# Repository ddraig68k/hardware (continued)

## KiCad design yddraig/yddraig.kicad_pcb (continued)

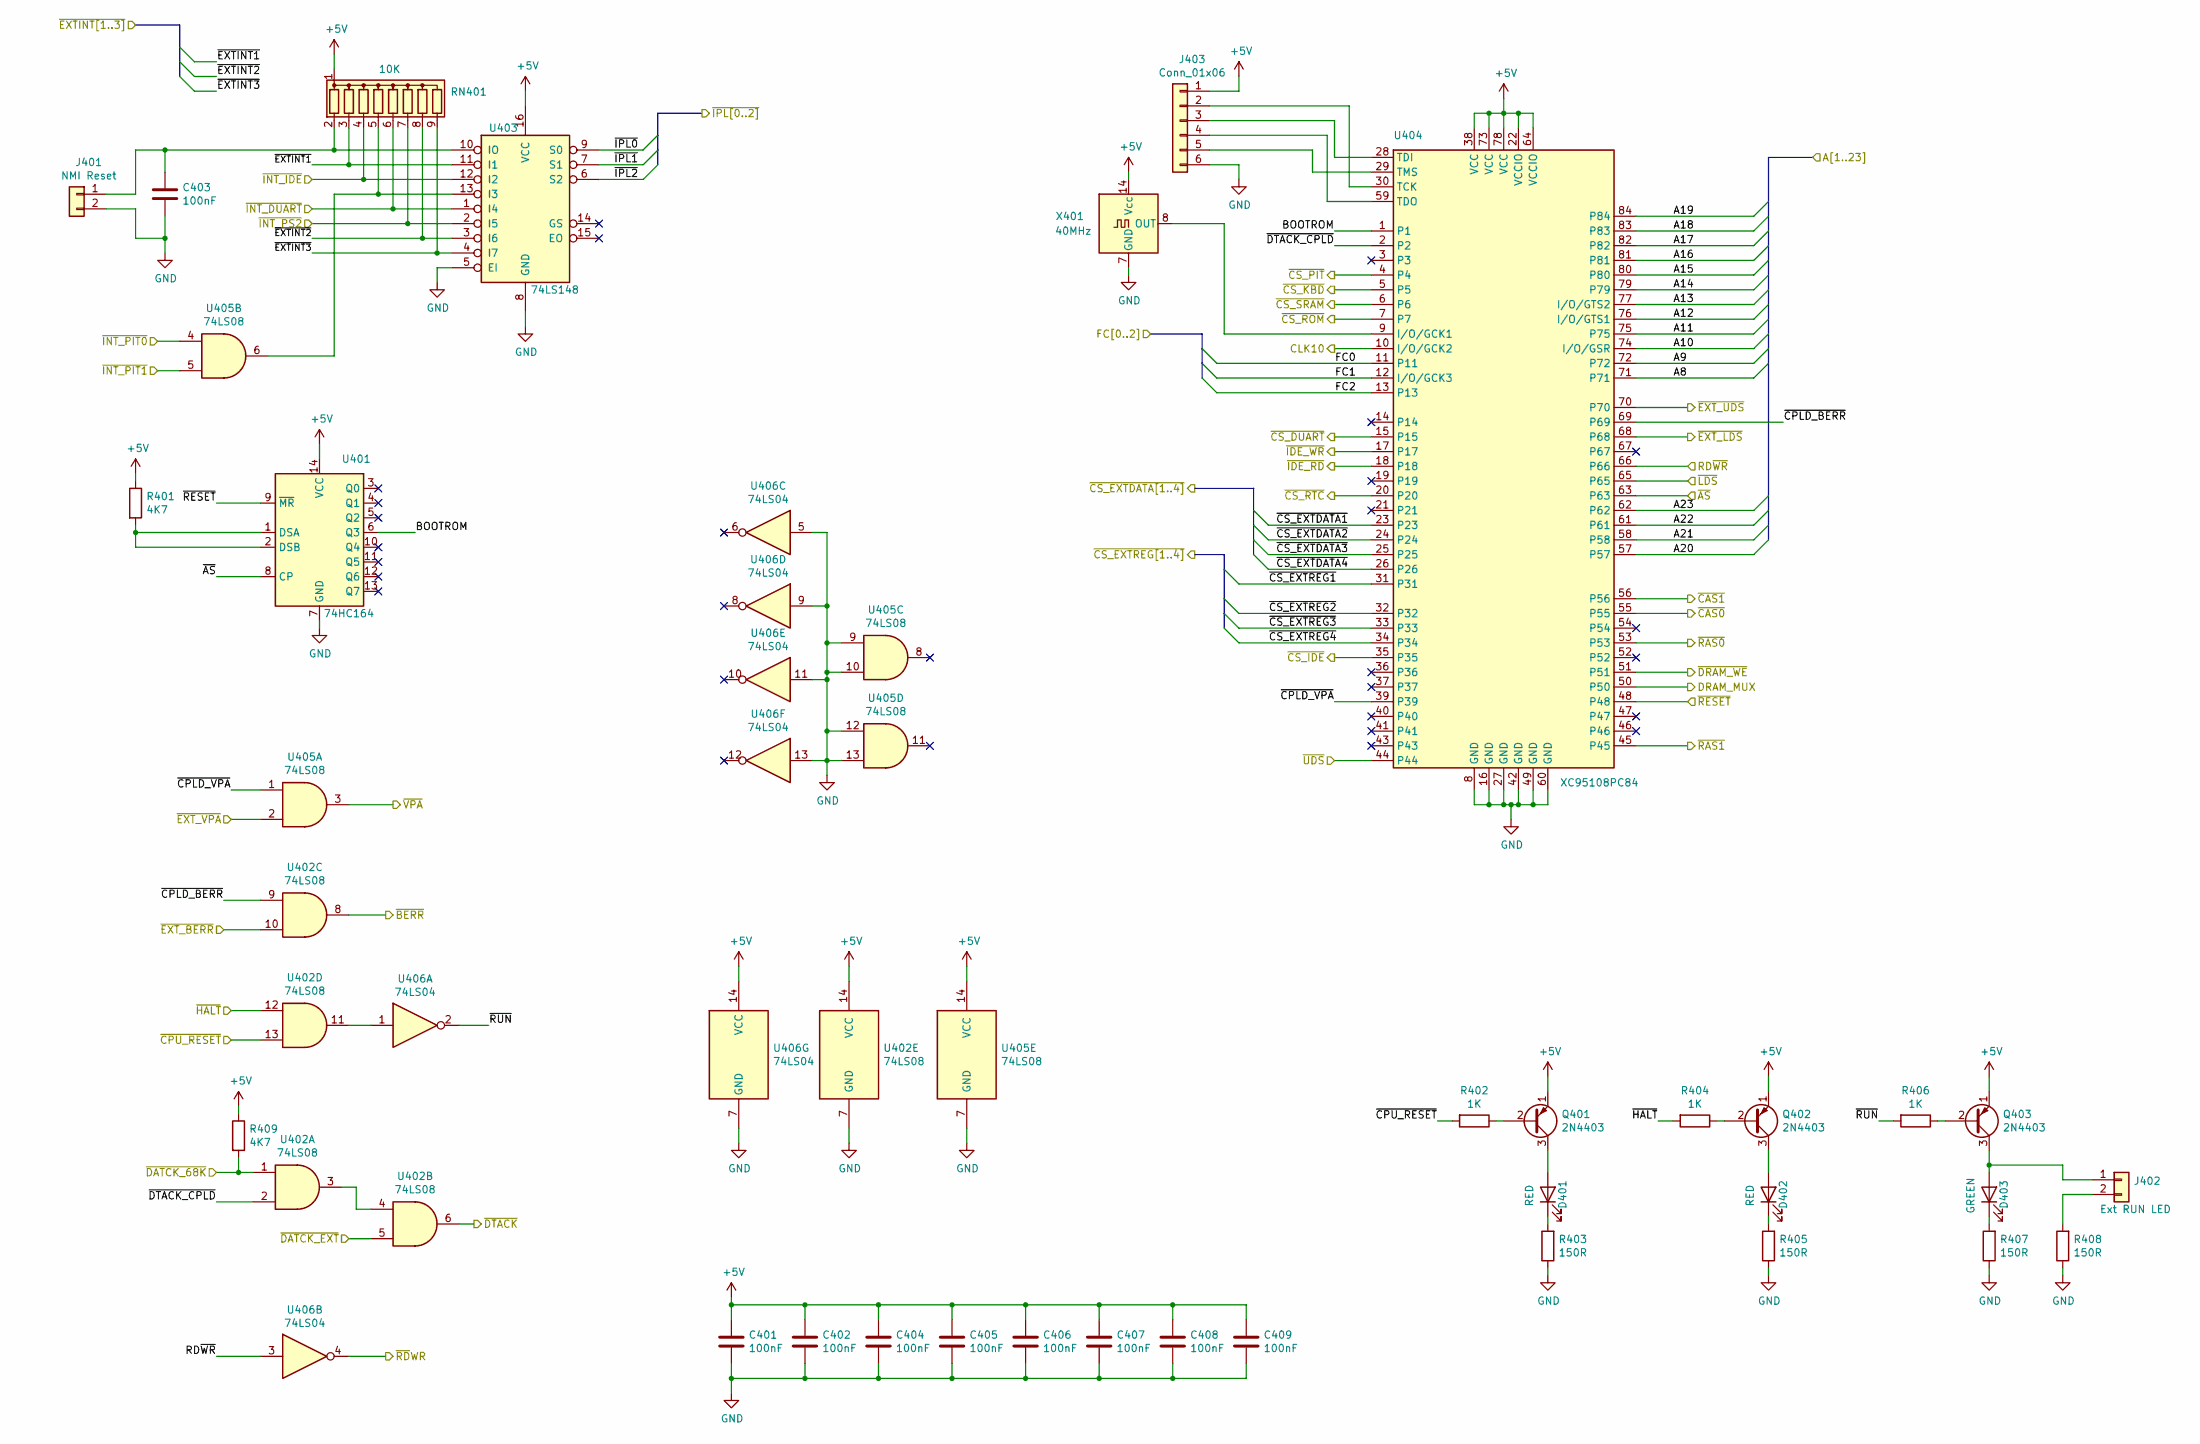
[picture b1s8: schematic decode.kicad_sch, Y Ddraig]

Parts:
C401, C402, C403, C404, C405, C406, C407, C408, C409: 100nF; C_Disc_D3.8mm_W2.6mm_P2.50mm
D401, D402: RED; LED_D5.0mm
D403: GREEN; LED_D5.0mm
J401: NMI Reset; PinHeader_1x02_P2.54mm_Vertical
J402: Ext RUN LED; PinHeader_1x02_P2.54mm_Vertical
J403: Conn_01x06; PinHeader_1x06_P2.54mm_Vertical
Q401, Q402, Q403: 2N4403; TO-92
R401, R409: 4K7; R_Axial_DIN0207_L6.3mm_D2.5mm_P10.16mm_Horizontal
R402, R404, R406: 1K; R_Axial_DIN0207_L6.3mm_D2.5mm_P10.16mm_Horizontal
R403, R405, R407, R408: 150R; R_Axial_DIN0207_L6.3mm_D2.5mm_P10.16mm_Horizontal
RN401: 10K; R_Array_SIP9
U401: 74HC164; DIP-14_W7.62mm_Socket
U402, U405: 74LS08; DIP-14_W7.62mm_Socket
U403: 74LS148; DIP-16_W7.62mm_Socket
U404: XC95108PC84; PLCC-84_THT-Socket
U406: 74LS04; DIP-14_W7.62mm_Socket
X401: 40MHz; Oscillator_DIP-14

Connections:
+5V: C401.1, C402.1, C404.1, C405.1, C406.1, C407.1, C408.1, C409.1, J403.1, Q401.1 (E), Q402.1 (E), Q403.1 (E), R401.1, R409.1, RN401.1 (common), U401.14 (VCC), U402.14 (VCC), U403.16 (VCC), U404.22 (VCCIO), U404.38 (VCC), U404.64 (VCCIO), U404.73 (VCC), U404.78 (VCC), U405.14 (VCC), U406.14 (VCC), X401.14 (Vcc); also elsewhere on the board
/CPU, RAM and ROM/A8: U404.71; also elsewhere on the board
/CPU, RAM and ROM/A9: U404.72; also elsewhere on the board
/CPU, RAM and ROM/A10: U404.74 (I/O/GSR); also elsewhere on the board
/CPU, RAM and ROM/A11: U404.75; also elsewhere on the board
/CPU, RAM and ROM/A12: U404.76 (I/O/GTS1); also elsewhere on the board
/CPU, RAM and ROM/A13: U404.77 (I/O/GTS2); also elsewhere on the board
/CPU, RAM and ROM/A14: U404.79; also elsewhere on the board
/CPU, RAM and ROM/A15: U404.80; also elsewhere on the board
/CPU, RAM and ROM/A16: U404.81; also elsewhere on the board
/CPU, RAM and ROM/A17: U404.82; also elsewhere on the board
/CPU, RAM and ROM/A18: U404.83; also elsewhere on the board
/CPU, RAM and ROM/A19: U404.84; also elsewhere on the board
/CPU, RAM and ROM/A20: U404.57; also elsewhere on the board
/CPU, RAM and ROM/A21: U404.58; also elsewhere on the board
/CPU, RAM and ROM/A22: U404.61; also elsewhere on the board
/CPU, RAM and ROM/A23: U404.62; also elsewhere on the board
/CPU, RAM and ROM/CLK10: U404.10 (I/O/GCK2); also elsewhere on the board
/CPU, RAM and ROM/FC0: U404.11; also elsewhere on the board
/CPU, RAM and ROM/FC1: U404.12 (I/O/GCK3); also elsewhere on the board
/CPU, RAM and ROM/FC2: U404.13; also elsewhere on the board
/CPU, RAM and ROM/RD~WR: U404.66, U406.3; also elsewhere on the board
/CPU, RAM and ROM/~AS: U401.8 (CP), U404.63; also elsewhere on the board
/CPU, RAM and ROM/~BERR: U402.8; also elsewhere on the board
/CPU, RAM and ROM/~CS_ROM: U404.7; also elsewhere on the board
/CPU, RAM and ROM/~CS_SRAM: U404.6; also elsewhere on the board
/CPU, RAM and ROM/~DTACK: U402.6; also elsewhere on the board
/CPU, RAM and ROM/~IPL0: U403.9 (S0); also elsewhere on the board
/CPU, RAM and ROM/~IPL1: U403.7 (S1); also elsewhere on the board
/CPU, RAM and ROM/~IPL2: U403.6 (S2); also elsewhere on the board
/CPU, RAM and ROM/~LDS: U404.65; also elsewhere on the board
/CPU, RAM and ROM/~RDWR: U406.4; also elsewhere on the board
/CPU, RAM and ROM/~UDS: U404.44; also elsewhere on the board
/CPU, RAM and ROM/~VPA: U405.3; also elsewhere on the board
/DRAM Interface/DRAM_MUX: U404.50; also elsewhere on the board
/DRAM Interface/~CAS0: U404.55; also elsewhere on the board
/DRAM Interface/~CAS1: U404.56; also elsewhere on the board
/DRAM Interface/~DRAM_WE: U404.51; also elsewhere on the board
/DRAM Interface/~RAS0: U404.53; also elsewhere on the board
/DRAM Interface/~RAS1: U404.45; also elsewhere on the board
/Decode and Logic/BOOTROM: U401.6 (Q3), U404.1
/Decode and Logic/~CPLD_BERR: U402.9, U404.69
/Decode and Logic/~CPLD_VPA: U404.39, U405.1
/Decode and Logic/~CPU_RESET: R402.2, U402.13; also elsewhere on the board
/Decode and Logic/~CS_DUART: U404.15; also elsewhere on the board
/Decode and Logic/~CS_IDE: U404.35; also elsewhere on the board
/Decode and Logic/~CS_KBD: U404.5; also elsewhere on the board
/Decode and Logic/~CS_PIT: U404.4; also elsewhere on the board
/Decode and Logic/~CS_RTC: U404.20; also elsewhere on the board
/Decode and Logic/~DATCK_EXT: U402.5; also elsewhere on the board
/Decode and Logic/~DTACK_CPLD: U402.2, U404.2
/Decode and Logic/~EXTINT1: RN401.3 (R2), U403.11 (I1); also elsewhere on the board
/Decode and Logic/~EXTINT2: RN401.8 (R7), U403.3 (I6); also elsewhere on the board
/Decode and Logic/~EXTINT3: RN401.9 (R8), U403.4 (I7); also elsewhere on the board
/Decode and Logic/~EXT_BERR: U402.10; also elsewhere on the board
/Decode and Logic/~EXT_LDS: U404.68; also elsewhere on the board
/Decode and Logic/~EXT_UDS: U404.70; also elsewhere on the board
/Decode and Logic/~HALT: R404.2, U402.12; also elsewhere on the board
/Decode and Logic/~IDE_RD: U404.18; also elsewhere on the board
/Decode and Logic/~IDE_WR: U404.17; also elsewhere on the board
/Decode and Logic/~INT_DUART: RN401.6 (R5), U403.1 (I4); also elsewhere on the board
/Decode and Logic/~INT_IDE: RN401.4 (R3), U403.12 (I2); also elsewhere on the board
/Decode and Logic/~INT_PIT0: U405.4; also elsewhere on the board
/Decode and Logic/~INT_PIT1: U405.5; also elsewhere on the board
/Decode and Logic/~INT_PS2: RN401.7 (R6), U403.2 (I5); also elsewhere on the board
/Decode and Logic/~RESET: U401.9 (~MR), U404.48; also elsewhere on the board
/Decode and Logic/~RUN: R406.2, U406.2
/Expansion Bus/Expansion Buffers/~CS_EXTDATA1: U404.23; also elsewhere on the board
/Expansion Bus/Expansion Buffers/~CS_EXTDATA2: U404.24; also elsewhere on the board
/Expansion Bus/Expansion Buffers/~CS_EXTDATA3: U404.25; also elsewhere on the board
/Expansion Bus/Expansion Buffers/~CS_EXTDATA4: U404.26; also elsewhere on the board
/Expansion Bus/Expansion Buffers/~CS_EXTREG1: U404.31; also elsewhere on the board
/Expansion Bus/Expansion Buffers/~CS_EXTREG2: U404.32; also elsewhere on the board
/Expansion Bus/Expansion Buffers/~CS_EXTREG3: U404.33; also elsewhere on the board
/Expansion Bus/Expansion Buffers/~CS_EXTREG4: U404.34; also elsewhere on the board
/Expansion Bus/~EXTVPA: U405.2; also elsewhere on the board
/Peripherals/~DTACK_68K: R409.2, U402.1; also elsewhere on the board
GND: C401.2, C402.2, C403.2, C404.2, C405.2, C406.2, C407.2, C408.2, C409.2, J401.2, J403.6, R403.1, R405.1, R407.1, R408.1, U401.7 (GND), U402.7 (GND), U403.5 (EI), U403.8 (GND), U404.8 (GND), U404.16 (GND), U404.27 (GND), U404.42 (GND), U404.49 (GND), U404.60 (GND), U405.7 (GND), U405.9, U405.10, U405.12, U405.13, U406.5, U406.7 (GND), U406.9, U406.11, U406.13, X401.7 (GND); also elsewhere on the board
unnamed: D401.2 (A), Q401.3 (C)
unnamed: D401.1 (K), R403.2
unnamed: D402.2 (A), Q402.3 (C)
unnamed: D402.1 (K), R405.2
unnamed: D403.2 (A), J402.1, Q403.3 (C)
unnamed: D403.1 (K), R407.2
unnamed: C403.1, J401.1, RN401.2 (R1), U403.10 (IO)
unnamed: J402.2, R408.2
unnamed: J403.2, U404.30 (TCK)
unnamed: J403.3, U404.28 (TDI)
unnamed: J403.4, U404.59 (TDO)
unnamed: J403.5, U404.29 (TMS)
unnamed: Q401.2 (B), R402.1
unnamed: Q402.2 (B), R404.1
unnamed: Q403.2 (B), R406.1
unnamed: RN401.5 (R4), U403.13 (I3), U405.6
unnamed: R401.2, U401.1 (DSA), U401.2 (DSB)
unnamed: U402.3, U402.4
unnamed: U402.11, U406.1
unnamed: U404.9 (I/O/GCK1), X401.8 (OUT)

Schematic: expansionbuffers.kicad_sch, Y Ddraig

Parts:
C901, C902, C903, C904, C905, C906, C907: 100nF; C_Disc_D3.8mm_W2.6mm_P2.50mm
RN901, RN902, RN903, RN904, RN905: 22R; DIP-16_W7.62mm
RN906, RN907: 10K; R_Array_SIP9
U901, U902, U903: 74LS541; DIP-20_W7.62mm_Socket
U904, U905, U906, U907: 74LS245; DIP-20_W7.62mm_Socket

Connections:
+5V: C901.1, C902.1, C903.1, C904.1, C905.1, C906.1, C907.1, U901.20 (VCC), U902.20 (VCC), U903.20 (VCC), U904.20 (VCC), U905.20 (VCC), U906.20 (VCC), U907.20 (VCC); also elsewhere on the board
/CPU, RAM and ROM/A1: U901.2 (A0); also elsewhere on the board
/CPU, RAM and ROM/A2: U901.3 (A1); also elsewhere on the board
/CPU, RAM and ROM/A3: U901.4 (A2); also elsewhere on the board
/CPU, RAM and ROM/A4: U901.5 (A3); also elsewhere on the board
/CPU, RAM and ROM/A5: U901.6 (A4); also elsewhere on the board
/CPU, RAM and ROM/A6: U901.7 (A5); also elsewhere on the board
/CPU, RAM and ROM/A7: U901.8 (A6); also elsewhere on the board
/CPU, RAM and ROM/A8: U901.9 (A7); also elsewhere on the board
/CPU, RAM and ROM/A9: U902.2 (A0); also elsewhere on the board
/CPU, RAM and ROM/A10: U902.3 (A1); also elsewhere on the board
/CPU, RAM and ROM/A11: U902.4 (A2); also elsewhere on the board
/CPU, RAM and ROM/A12: U902.5 (A3); also elsewhere on the board
/CPU, RAM and ROM/A13: U902.6 (A4); also elsewhere on the board
/CPU, RAM and ROM/A14: U902.7 (A5); also elsewhere on the board
/CPU, RAM and ROM/A15: U902.8 (A6); also elsewhere on the board
/CPU, RAM and ROM/A16: U902.9 (A7); also elsewhere on the board
/CPU, RAM and ROM/A17: U903.2 (A0); also elsewhere on the board
/CPU, RAM and ROM/A18: U903.3 (A1); also elsewhere on the board
/CPU, RAM and ROM/A19: U903.4 (A2); also elsewhere on the board
/CPU, RAM and ROM/CLK10: U904.11 (B7); also elsewhere on the board
/CPU, RAM and ROM/E: U904.12 (B6); also elsewhere on the board
/CPU, RAM and ROM/RD~WR: U904.15 (B3); also elsewhere on the board
/CPU, RAM and ROM/~AS: U901.1 (G1), U902.1 (G1), U903.1 (G1), U904.14 (B4); also elsewhere on the board
/CPU, RAM and ROM/~LDS: U904.17 (B1); also elsewhere on the board
/CPU, RAM and ROM/~RDWR: U905.1 (A->B), U906.1 (A->B); also elsewhere on the board
/CPU, RAM and ROM/~UDS: U904.16 (B2); also elsewhere on the board
/CPU, RAM and ROM/~VMA: U904.13 (B5); also elsewhere on the board
/Decode and Logic/~EXT_LDS: U905.19 (CE); also elsewhere on the board
/Decode and Logic/~EXT_UDS: U906.19 (CE); also elsewhere on the board
/Decode and Logic/~RESET: U904.18 (B0); also elsewhere on the board
/Expansion Bus/BA1: RN901.16 (R1.2); also elsewhere on the board
/Expansion Bus/BA2: RN901.15 (R2.2); also elsewhere on the board
/Expansion Bus/BA3: RN901.14 (R3.2); also elsewhere on the board
/Expansion Bus/BA4: RN901.13 (R4.2); also elsewhere on the board
/Expansion Bus/BA5: RN901.12 (R5.2); also elsewhere on the board
/Expansion Bus/BA6: RN901.11 (R6.2); also elsewhere on the board
/Expansion Bus/BA7: RN901.10 (R7.2); also elsewhere on the board
/Expansion Bus/BA8: RN901.9 (R8.2); also elsewhere on the board
/Expansion Bus/BA9: RN902.16 (R1.2); also elsewhere on the board
/Expansion Bus/BA10: RN902.15 (R2.2); also elsewhere on the board
/Expansion Bus/BA11: RN902.14 (R3.2); also elsewhere on the board
/Expansion Bus/BA12: RN902.13 (R4.2); also elsewhere on the board
/Expansion Bus/BA13: RN902.12 (R5.2); also elsewhere on the board
/Expansion Bus/BA14: RN902.11 (R6.2); also elsewhere on the board
/Expansion Bus/BA15: RN902.10 (R7.2); also elsewhere on the board
/Expansion Bus/BA16: RN902.9 (R8.2); also elsewhere on the board
/Expansion Bus/BA17: RN903.16 (R1.2); also elsewhere on the board
/Expansion Bus/BA18: RN903.15 (R2.2); also elsewhere on the board
/Expansion Bus/BA19: RN903.14 (R3.2); also elsewhere on the board
/Expansion Bus/BCLK10: U904.9 (A7); also elsewhere on the board
/Expansion Bus/BD0: RN904.16 (R1.2), RN906.2 (R1); also elsewhere on the board
/Expansion Bus/BD1: RN904.15 (R2.2), RN906.3 (R2); also elsewhere on the board
/Expansion Bus/BD2: RN904.14 (R3.2), RN906.4 (R3); also elsewhere on the board
/Expansion Bus/BD3: RN904.13 (R4.2), RN906.5 (R4); also elsewhere on the board
/Expansion Bus/BD4: RN904.12 (R5.2), RN906.6 (R5); also elsewhere on the board
/Expansion Bus/BD5: RN904.11 (R6.2), RN906.7 (R6); also elsewhere on the board
/Expansion Bus/BD6: RN904.10 (R7.2), RN906.8 (R7); also elsewhere on the board
/Expansion Bus/BD7: RN904.9 (R8.2), RN906.9 (R8); also elsewhere on the board
/Expansion Bus/BD8: RN905.16 (R1.2), RN907.2 (R1); also elsewhere on the board
/Expansion Bus/BD9: RN905.15 (R2.2), RN907.3 (R2); also elsewhere on the board
/Expansion Bus/BD10: RN905.14 (R3.2), RN907.4 (R3); also elsewhere on the board
/Expansion Bus/BD11: RN905.13 (R4.2), RN907.5 (R4); also elsewhere on the board
/Expansion Bus/BD12: RN905.12 (R5.2), RN907.6 (R5); also elsewhere on the board
/Expansion Bus/BD13: RN905.11 (R6.2), RN907.7 (R6); also elsewhere on the board
/Expansion Bus/BD14: RN905.10 (R7.2), RN907.8 (R7); also elsewhere on the board
/Expansion Bus/BD15: RN905.9 (R8.2), RN907.9 (R8); also elsewhere on the board
/Expansion Bus/BE: U904.8 (A6); also elsewhere on the board
/Expansion Bus/BRD~WR: U904.5 (A3); also elsewhere on the board
/Expansion Bus/Expansion Buffers/~CS_EXTDATA1: U907.14 (B4); also elsewhere on the board
/Expansion Bus/Expansion Buffers/~CS_EXTDATA2: U907.13 (B5); also elsewhere on the board
/Expansion Bus/Expansion Buffers/~CS_EXTDATA3: U907.12 (B6); also elsewhere on the board
/Expansion Bus/Expansion Buffers/~CS_EXTDATA4: U907.11 (B7); also elsewhere on the board
/Expansion Bus/Expansion Buffers/~CS_EXTREG1: U907.18 (B0); also elsewhere on the board
/Expansion Bus/Expansion Buffers/~CS_EXTREG2: U907.17 (B1); also elsewhere on the board
/Expansion Bus/Expansion Buffers/~CS_EXTREG3: U907.16 (B2); also elsewhere on the board
/Expansion Bus/Expansion Buffers/~CS_EXTREG4: U907.15 (B3); also elsewhere on the board
/Expansion Bus/~BAS: U904.6 (A4); also elsewhere on the board
/Expansion Bus/~BCS_EXTDATA1: U907.6 (A4); also elsewhere on the board
/Expansion Bus/~BCS_EXTDATA2: U907.7 (A5); also elsewhere on the board
/Expansion Bus/~BCS_EXTDATA3: U907.8 (A6); also elsewhere on the board
/Expansion Bus/~BCS_EXTDATA4: U907.9 (A7); also elsewhere on the board
/Expansion Bus/~BCS_EXTREG1: U907.2 (A0); also elsewhere on the board
/Expansion Bus/~BCS_EXTREG2: U907.3 (A1); also elsewhere on the board
/Expansion Bus/~BCS_EXTREG3: U907.4 (A2); also elsewhere on the board
/Expansion Bus/~BCS_EXTREG4: U907.5 (A3); also elsewhere on the board
/Expansion Bus/~BLDS: U904.3 (A1); also elsewhere on the board
/Expansion Bus/~BRESET: U904.2 (A0); also elsewhere on the board
/Expansion Bus/~BUDS: U904.4 (A2); also elsewhere on the board
/Expansion Bus/~BVMA: U904.7 (A5); also elsewhere on the board
/Peripherals/D0: U905.2 (A0); also elsewhere on the board
/Peripherals/D1: U905.3 (A1); also elsewhere on the board
/Peripherals/D2: U905.4 (A2); also elsewhere on the board
/Peripherals/D3: U905.5 (A3); also elsewhere on the board
/Peripherals/D4: U905.6 (A4); also elsewhere on the board
/Peripherals/D5: U905.7 (A5); also elsewhere on the board
/Peripherals/D6: U905.8 (A6); also elsewhere on the board
/Peripherals/D7: U905.9 (A7); also elsewhere on the board
/Peripherals/D8: U906.2 (A0); also elsewhere on the board
/Peripherals/D9: U906.3 (A1); also elsewhere on the board
/Peripherals/D10: U906.4 (A2); also elsewhere on the board
/Peripherals/D11: U906.5 (A3); also elsewhere on the board
/Peripherals/D12: U906.6 (A4); also elsewhere on the board
/Peripherals/D13: U906.7 (A5); also elsewhere on the board
/Peripherals/D14: U906.8 (A6); also elsewhere on the board
/Peripherals/D15: U906.9 (A7); also elsewhere on the board
GND: C901.2, C902.2, C903.2, C904.2, C905.2, C906.2, C907.2, RN906.1 (common), RN907.1 (common), U901.10 (GND), U901.19 (G2), U902.10 (GND), U902.19 (G2), U903.5 (A3), U903.6 (A4), U903.7 (A5), U903.8 (A6), U903.9 (A7), U903.10 (GND), U903.19 (G2), U904.1 (A->B), U904.10 (GND), U904.19 (CE), U905.10 (GND), U906.10 (GND), U907.1 (A->B), U907.10 (GND), U907.19 (CE); also elsewhere on the board
unnamed: RN901.1 (R1.1), U901.18 (Y0)
unnamed: RN901.2 (R2.1), U901.17 (Y1)
unnamed: RN901.3 (R3.1), U901.16 (Y2)
unnamed: RN901.4 (R4.1), U901.15 (Y3)
unnamed: RN901.5 (R5.1), U901.14 (Y4)
unnamed: RN901.6 (R6.1), U901.13 (Y5)
unnamed: RN901.7 (R7.1), U901.12 (Y6)
unnamed: RN901.8 (R8.1), U901.11 (Y7)
unnamed: RN902.1 (R1.1), U902.18 (Y0)
unnamed: RN902.2 (R2.1), U902.17 (Y1)
unnamed: RN902.3 (R3.1), U902.16 (Y2)
unnamed: RN902.4 (R4.1), U902.15 (Y3)
unnamed: RN902.5 (R5.1), U902.14 (Y4)
unnamed: RN902.6 (R6.1), U902.13 (Y5)
unnamed: RN902.7 (R7.1), U902.12 (Y6)
unnamed: RN902.8 (R8.1), U902.11 (Y7)
unnamed: RN903.1 (R1.1), U903.18 (Y0)
unnamed: RN903.2 (R2.1), U903.17 (Y1)
unnamed: RN903.3 (R3.1), U903.16 (Y2)
unnamed: RN903.4 (R4.1), U903.15 (Y3)
unnamed: RN903.5 (R5.1), U903.14 (Y4)
unnamed: RN903.6 (R6.1), U903.13 (Y5)
unnamed: RN903.7 (R7.1), U903.12 (Y6)
unnamed: RN903.8 (R8.1), U903.11 (Y7)
unnamed: RN904.1 (R1.1), U905.18 (B0)
unnamed: RN904.2 (R2.1), U905.17 (B1)
unnamed: RN904.3 (R3.1), U905.16 (B2)
unnamed: RN904.4 (R4.1), U905.15 (B3)
unnamed: RN904.5 (R5.1), U905.14 (B4)
unnamed: RN904.6 (R6.1), U905.13 (B5)
unnamed: RN904.7 (R7.1), U905.12 (B6)
unnamed: RN904.8 (R8.1), U905.11 (B7)
unnamed: RN905.1 (R1.1), U906.18 (B0)
unnamed: RN905.2 (R2.1), U906.17 (B1)
unnamed: RN905.3 (R3.1), U906.16 (B2)
unnamed: RN905.4 (R4.1), U906.15 (B3)
unnamed: RN905.5 (R5.1), U906.14 (B4)
unnamed: RN905.6 (R6.1), U906.13 (B5)
unnamed: RN905.7 (R7.1), U906.12 (B6)
unnamed: RN905.8 (R8.1), U906.11 (B7)

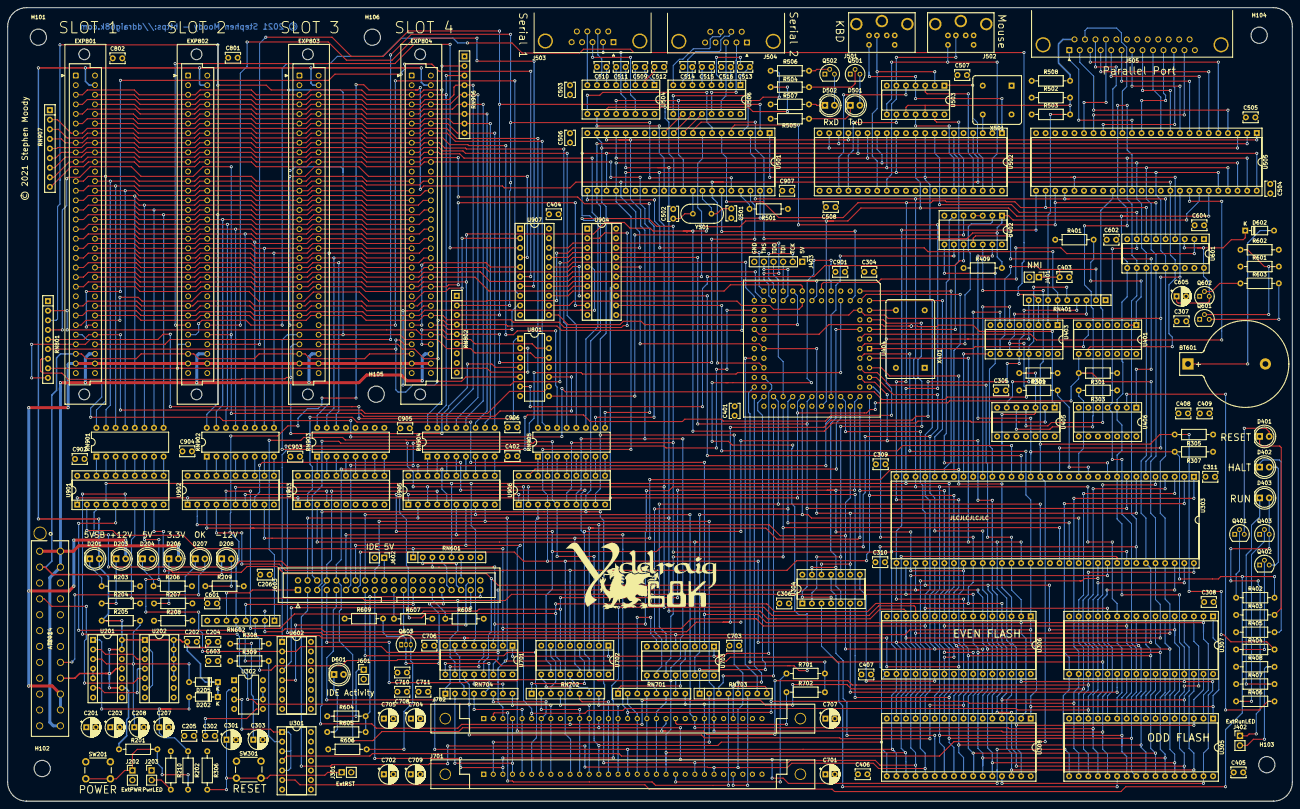
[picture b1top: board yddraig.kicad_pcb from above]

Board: 4 copper layers, 340.0 x 210.0 mm, 223 parts (0 on the bottom side), 370 nets.

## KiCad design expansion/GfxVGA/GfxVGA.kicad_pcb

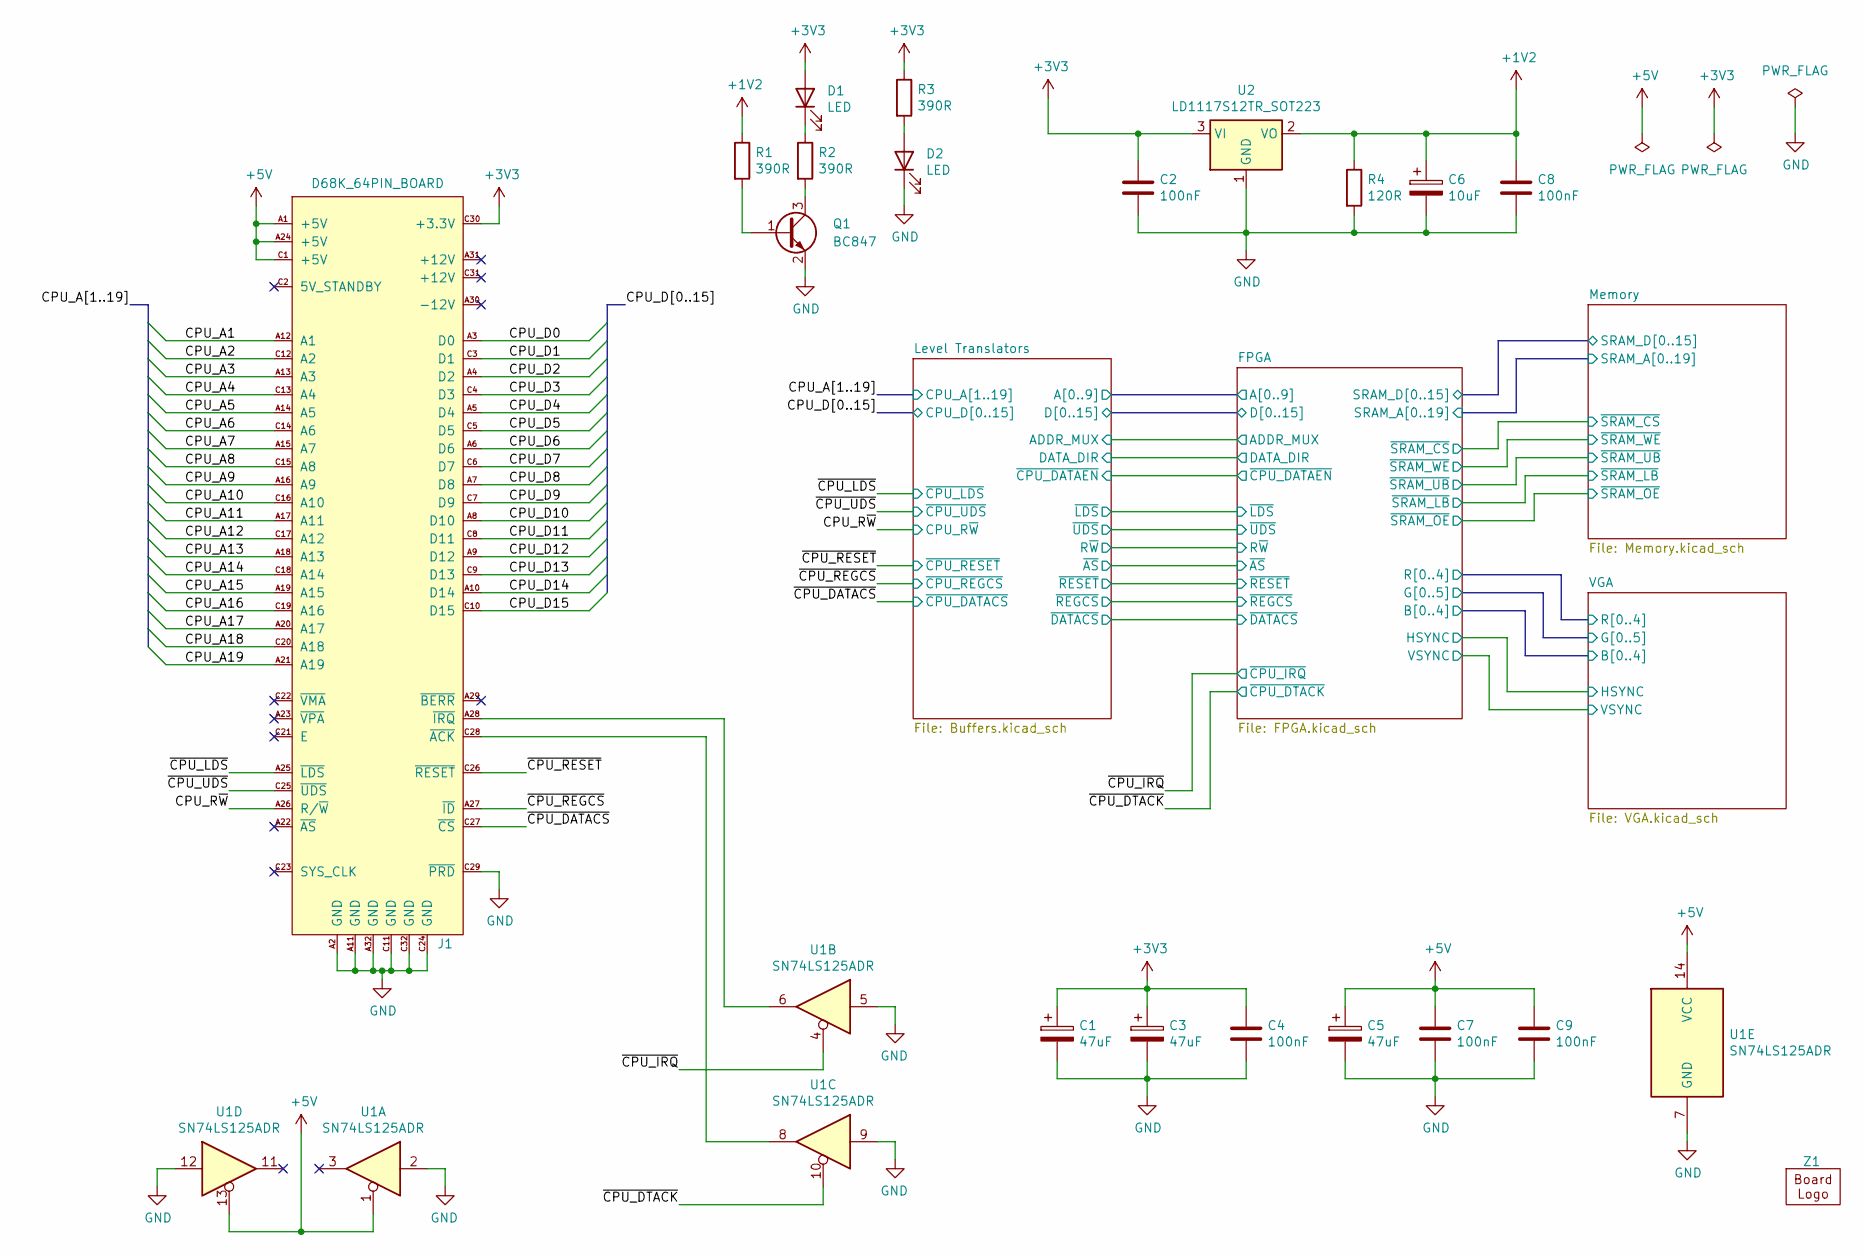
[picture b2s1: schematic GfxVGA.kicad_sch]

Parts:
C1, C3, C5: 47uF; CP_Elec_4x5.3
C2, C4, C7, C8, C9: 100nF; C_0805_2012Metric
C6: 10uF; CP_Elec_4x5.3
D1, D2: LED; LED_1206_3216Metric
J1: D68K_64PIN_BOARD; DIN41612_C_2x32_Male_Horizontal_THT
Q1: BC847; SOT-23
R1, R2, R3: 390R; R_0805_2012Metric
R4: 120R; R_0805_2012Metric
U1: SN74LS125ADR; SO-14_3.9x8.65mm_P1.27mm
U2: LD1117S12TR_SOT223; SOT-223-3_TabPin2
Z1: Ddraig68k-26mm

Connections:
+1V2: C6.1, C8.1, R1.1, R4.1, U2.2 (VO); also elsewhere on the board
+3V3: C1.1, C2.1, C3.1, C4.1, D1.2 (A), J1.C30 (+3.3V), R3.1, U2.3 (VI); also elsewhere on the board
+5V: C5.1, C7.1, C9.1, J1.A1 (+5V), J1.A24 (+5V), J1.C1 (+5V), U1.1, U1.13, U1.14 (VCC); also elsewhere on the board
/CPU_A1: J1.A12 (A1); also elsewhere on the board
/CPU_A2: J1.C12 (A2); also elsewhere on the board
/CPU_A3: J1.A13 (A3); also elsewhere on the board
/CPU_A4: J1.C13 (A4); also elsewhere on the board
/CPU_A5: J1.A14 (A5); also elsewhere on the board
/CPU_A6: J1.C14 (A6); also elsewhere on the board
/CPU_A7: J1.A15 (A7); also elsewhere on the board
/CPU_A8: J1.C15 (A8); also elsewhere on the board
/CPU_A9: J1.A16 (A9); also elsewhere on the board
/CPU_A10: J1.C16 (A10); also elsewhere on the board
/CPU_A11: J1.A17 (A11); also elsewhere on the board
/CPU_A12: J1.C17 (A12); also elsewhere on the board
/CPU_A13: J1.A18 (A13); also elsewhere on the board
/CPU_A14: J1.C18 (A14); also elsewhere on the board
/CPU_A15: J1.A19 (A15); also elsewhere on the board
/CPU_A16: J1.C19 (A16); also elsewhere on the board
/CPU_A17: J1.A20 (A17); also elsewhere on the board
/CPU_A18: J1.C20 (A18); also elsewhere on the board
/CPU_A19: J1.A21 (A19); also elsewhere on the board
/CPU_D0: J1.A3 (D0); also elsewhere on the board
/CPU_D1: J1.C3 (D1); also elsewhere on the board
/CPU_D2: J1.A4 (D2); also elsewhere on the board
/CPU_D3: J1.C4 (D3); also elsewhere on the board
/CPU_D4: J1.A5 (D4); also elsewhere on the board
/CPU_D5: J1.C5 (D5); also elsewhere on the board
/CPU_D6: J1.A6 (D6); also elsewhere on the board
/CPU_D7: J1.C6 (D7); also elsewhere on the board
/CPU_D8: J1.A7 (D8); also elsewhere on the board
/CPU_D9: J1.C7 (D9); also elsewhere on the board
/CPU_D10: J1.A8 (D10); also elsewhere on the board
/CPU_D11: J1.C8 (D11); also elsewhere on the board
/CPU_D12: J1.A9 (D12); also elsewhere on the board
/CPU_D13: J1.C9 (D13); also elsewhere on the board
/CPU_D14: J1.A10 (D14); also elsewhere on the board
/CPU_D15: J1.C10 (D15); also elsewhere on the board
/CPU_R~W: J1.A26 (R/~W); also elsewhere on the board
/~CPU_DATACS: J1.C27 (~CS); also elsewhere on the board
/~CPU_DTACK: U1.10; also elsewhere on the board
/~CPU_IRQ: U1.4; also elsewhere on the board
/~CPU_LDS: J1.A25 (~LDS); also elsewhere on the board
/~CPU_REGCS: J1.A27 (~ID); also elsewhere on the board
/~CPU_RESET: J1.C26 (~RESET); also elsewhere on the board
/~CPU_UDS: J1.C25 (~UDS); also elsewhere on the board
GND: C1.2, C2.2, C3.2, C4.2, C5.2, C6.2, C7.2, C8.2, C9.2, D2.1 (K), J1.A2 (GND), J1.A11 (GND), J1.A32 (GND), J1.C11 (GND), J1.C24 (GND), J1.C29 (~PRD), J1.C32 (GND), Q1.2 (E), R4.2, U1.2, U1.5, U1.7 (GND), U1.9, U1.12, U2.1 (GND); also elsewhere on the board
unnamed: D1.1 (K), R2.1
unnamed: D2.2 (A), R3.2
unnamed: J1.C28 (~ACK), U1.8
unnamed: J1.A28 (~IRQ), U1.6
unnamed: Q1.1 (B), R1.2
unnamed: Q1.3 (C), R2.2
